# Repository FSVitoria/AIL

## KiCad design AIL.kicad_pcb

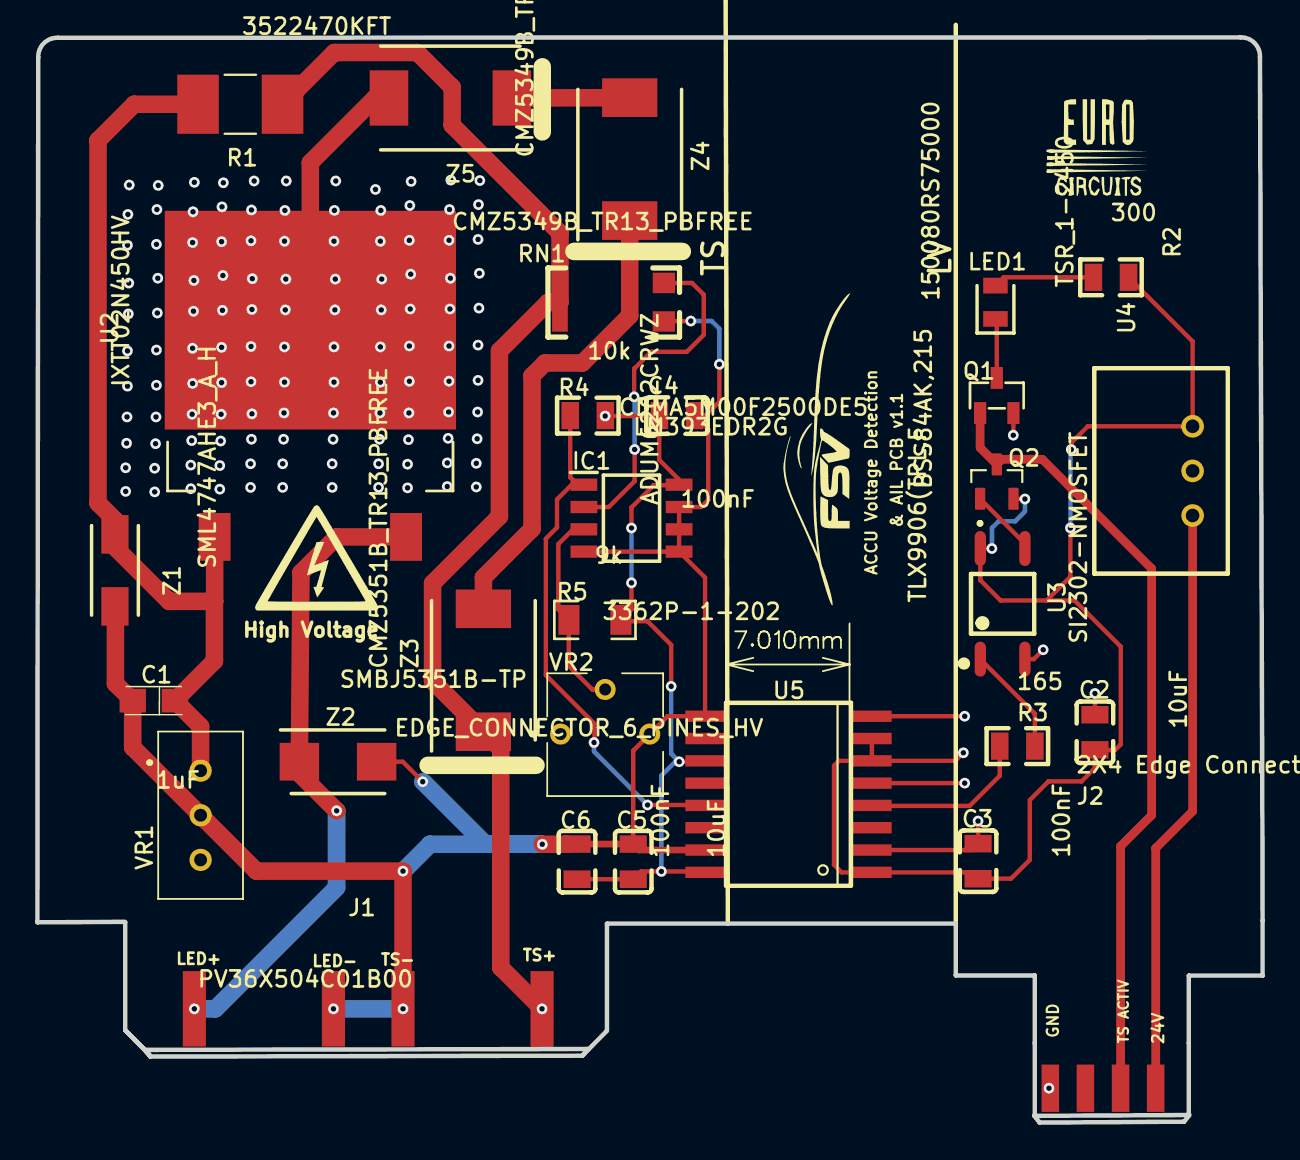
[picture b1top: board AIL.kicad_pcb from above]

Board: 2 copper layers, 69.8 x 61.8 mm, 29 parts (0 on the bottom side), 20 nets.

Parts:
C1: 1uF; CASE-A_3216
C2, C5: 10uF; C0805
C3, C4, C6: 100nF; C0805
IC1: LM393EDR2G; SOIC127P600X175-8N
J1: EDGE_CONNECTOR_6_PINES_HV
J2: 2X4 Edge Connector; 2X4 EDGE CONNECTOR
LED1: 150080RS75000; LEDC2012X80N
Q1: SI2302-NMOSFET; SOT-23-3_L2.9-W1.3-P1.90-LS2.4-BR
Q2: BSS84AK,215; SOT95P230X110-3N
R1: 3522470KFT; RESC6332X120N
R2: 300; R0805
R3: 165; R0805
R4: 10k; R0805
R5: 9k; R1206
RN1: CDMA5M00F2500DE5; CDMA15M0D2500DE5
U2: IXTT02N450HV; IXTT
U3: TLX9906(TPL,F; SOIC-4_L3.6-W4.4-P2.54-LS7.0-TL
U4: TSR_1-2450; TSR-1-24120
U5: ADUM6202CRWZ; SOIC16E
VR1: PV36X504C01B00; PV36X253C01B00
VR2: 3362P-1-202; 3362P1103RLF
Z1: SML4747AHE3_A_H; DIONM5127X229N
Z2: SMBJ5351B-TP; DIOM5336X262N
Z3: CMZ5351B_TR13_PBFREE; DIOM7959X262N
Z4, Z5: CMZ5349B_TR13_PBFREE; DIOM7959X262N

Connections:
+5V: C2.2, C3.2, Q2.2, R2.2, U3.6, U4.3, U5.1, U5.6, U5.7
+5VISO: C4.2, C5.2, C6.2, IC1.8, R4.2, R5.2, U5.11, U5.16
+24V: J2.A4, U4.1
GND: C2.1, C3.1, J2.A1, Q1.2, U3.3, U4.2, U5.2, U5.5, U5.8
IC1_2: IC1.2, RN1.3
LED1_1: LED1.1, Q1.3
LED1_2: LED1.2, R2.1
LED+: J1.A1, J1.B1, U2.S, Z2.1
Q2_1: Q2.1, U3.4
R3_2: R3.2, U3.1
TS+: J1.A6, J1.B6, R1.2, RN1.1, Z3.1
TS-: C1.2, C4.1, C5.1, C6.1, IC1.4, IC1.5, IC1.6, IC1.7, J1.A3, J1.A4, J1.B3, J1.B4, RN1.2, U5.9, U5.15, VR1.2, VR2.3, Z1.2, Z2.2
TS_ACTIVE_ACCU: R3.1, U5.4
TS_ACTIVE_ACCU_OUT: J2.A3, Q1.1, Q2.3
U2_D: U2.D, Z5.2
U5_13: IC1.1, R4.1, U5.13
VR1_1: C1.1, R1.1, U2.G, VR1.1, Z1.1
VR2_2: IC1.3, R5.1, VR2.2
Z3_2: Z3.2, Z4.1
Z4_2: Z4.2, Z5.1
